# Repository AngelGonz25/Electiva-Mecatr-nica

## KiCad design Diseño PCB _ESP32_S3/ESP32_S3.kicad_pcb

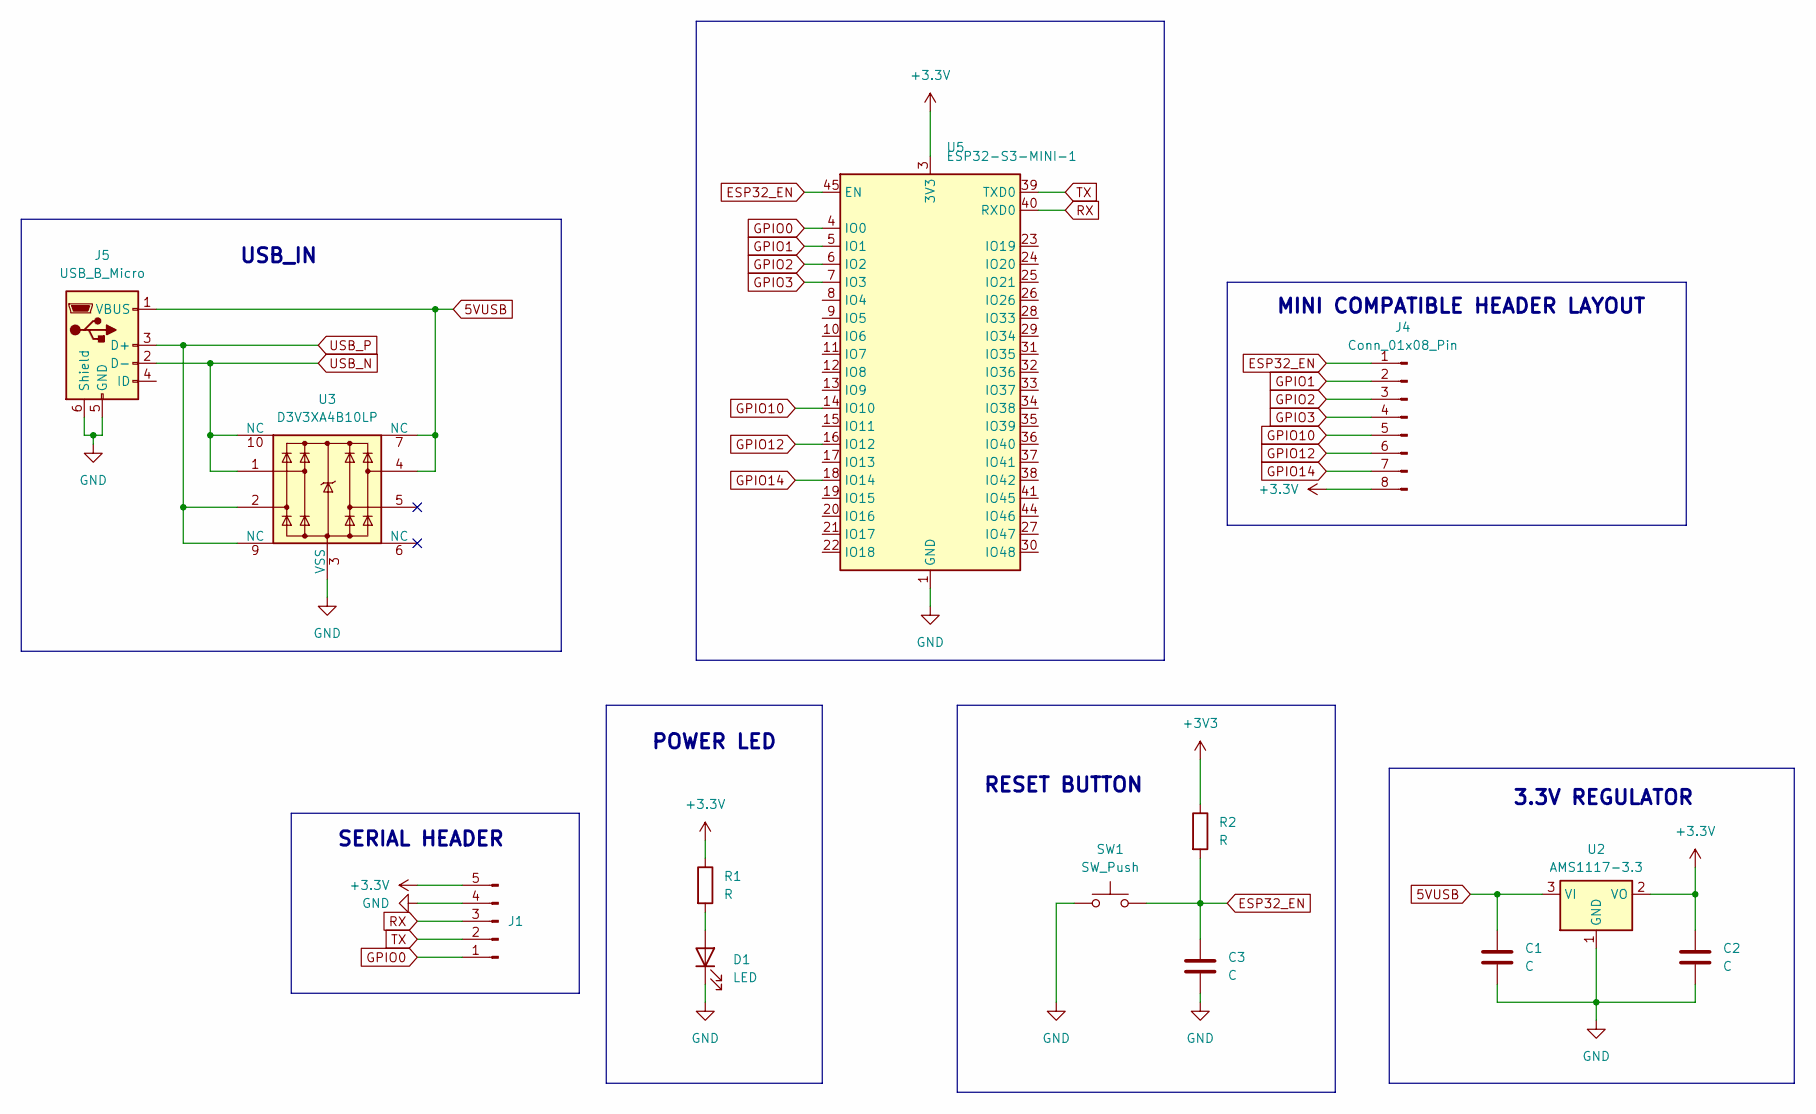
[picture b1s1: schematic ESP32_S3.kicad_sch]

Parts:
C1, C2: C; CP_EIA-2012-12_Kemet-R_Pad1.30x1.05mm_HandSolder
C3: C; CP_EIA-3216-10_Kemet-I_Pad1.58x1.35mm_HandSolder
D1: LED; LED_0402_1005Metric_Pad0.77x0.64mm_HandSolder
J1: Conn_01x05_Pin; PinHeader_1x05_P1.00mm_Vertical
J4: Conn_01x08_Pin; PinHeader_1x08_P1.00mm_Vertical
J5: USB_B_Micro; USB_Micro-B_GCT_USB3076-30-A
R1, R2: R; R_0805_2012Metric_Pad1.20x1.40mm_HandSolder
SW1: SW_Push; SW_SPST_PTS647_Sx50
U2: AMS1117-3.3; SOT-223-3_TabPin2
U3: D3V3XA4B10LP; Diodes_UDFN-10_1.0x2.5mm_P0.5mm
U5: ESP32-S3-MINI-1; ESP32-S2-MINI-1

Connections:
5VUSB: C1.1, J5.1 (VBUS), U2.3 (VI), U3.4, U3.7 (NC)
+3.3V: C2.1, J1.5, J4.8, R1.1, U2.2 (VO), U5.3 (3V3)
+3V3: R2.1
ESP32_EN: C3.1, J4.1, R2.2, SW1.2, U5.45 (EN)
GND: C1.2, C2.2, C3.2, D1.1 (K), J1.4, J5.5 (GND), J5.6 (Shield), SW1.1, U2.1 (GND), U3.3 (VSS), U3.8 (VSS), U5.1 (GND), U5.2 (GND), U5.42 (GND), U5.43 (GND), U5.46 (GND), U5.47 (GND), U5.48 (GND), U5.49 (GND), U5.50 (GND), U5.51 (GND), U5.52 (GND), U5.53 (GND), U5.54 (GND), U5.55 (GND), U5.56 (GND), U5.57 (GND), U5.58 (GND), U5.59 (GND), U5.60 (GND), U5.61 (GND), U5.62 (GND), U5.63 (GND), U5.64 (GND), U5.65 (GND)
GPIO0: J1.1, U5.4 (IO0)
GPIO1: J4.2, U5.5 (IO1)
GPIO2: J4.3, U5.6 (IO2)
GPIO3: J4.4, U5.7 (IO3)
GPIO10: J4.5, U5.14 (IO10)
GPIO12: J4.6, U5.16 (IO12)
GPIO14: J4.7, U5.18 (IO14)
unnamed: D1.2 (A), R1.2
RX: J1.3, U5.40 (RXD0)
TX: J1.2, U5.39 (TXD0)
USB_N: J5.2 (D-), U3.1, U3.10 (NC)
USB_P: J5.3 (D+), U3.2, U3.9 (NC)

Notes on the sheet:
RESET BUTTON
MINI COMPATIBLE HEADER LAYOUT
POWER LED
USB_IN
SERIAL HEADER
3.3V REGULATOR

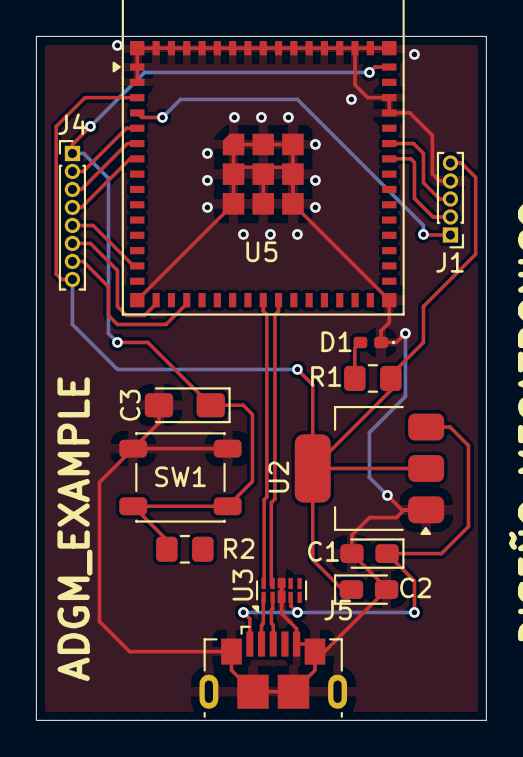
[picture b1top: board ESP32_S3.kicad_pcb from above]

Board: 2 copper layers, 25.0 x 38.0 mm, 13 parts (0 on the bottom side), 16 nets.
